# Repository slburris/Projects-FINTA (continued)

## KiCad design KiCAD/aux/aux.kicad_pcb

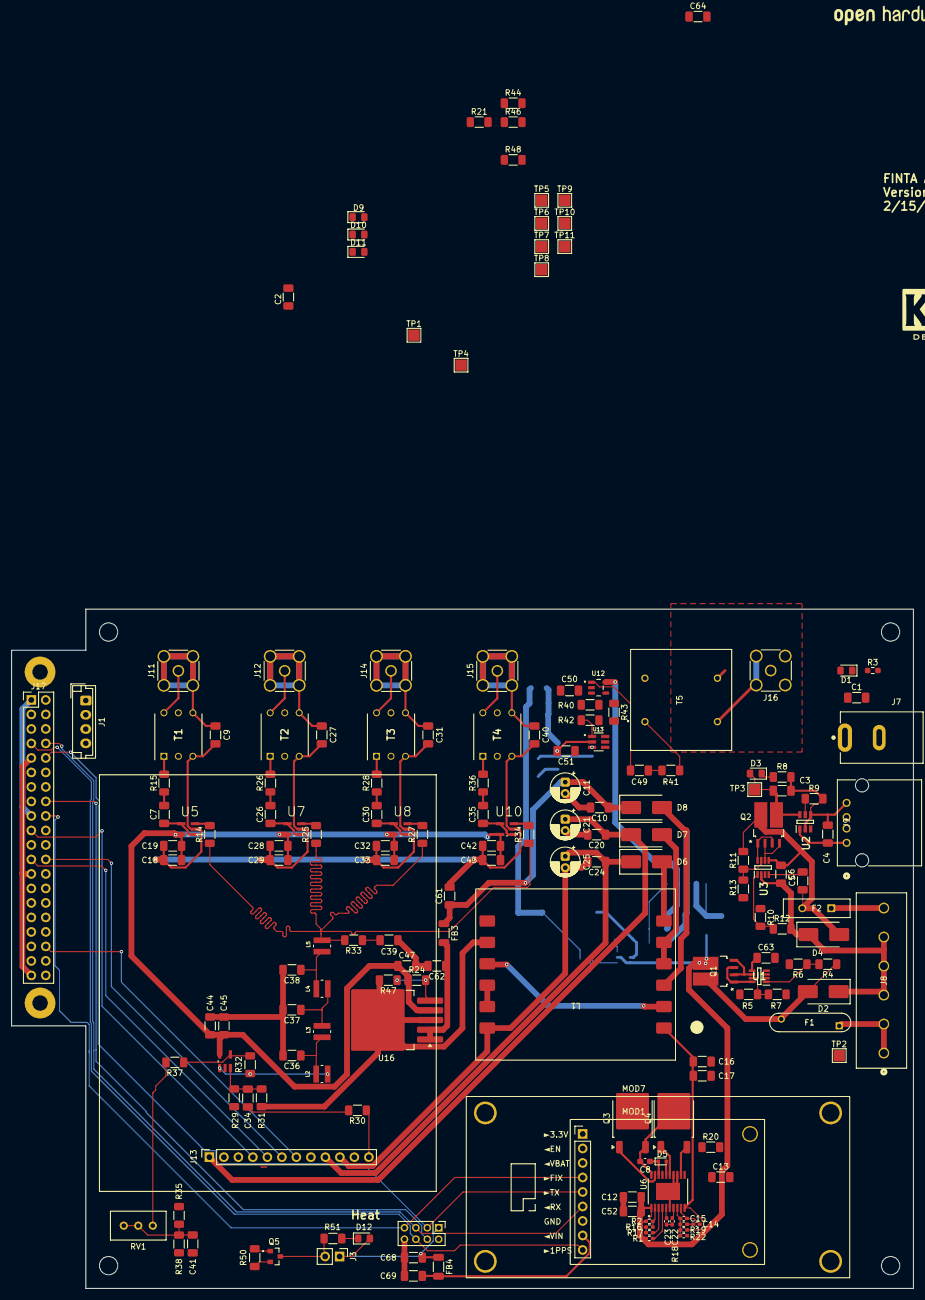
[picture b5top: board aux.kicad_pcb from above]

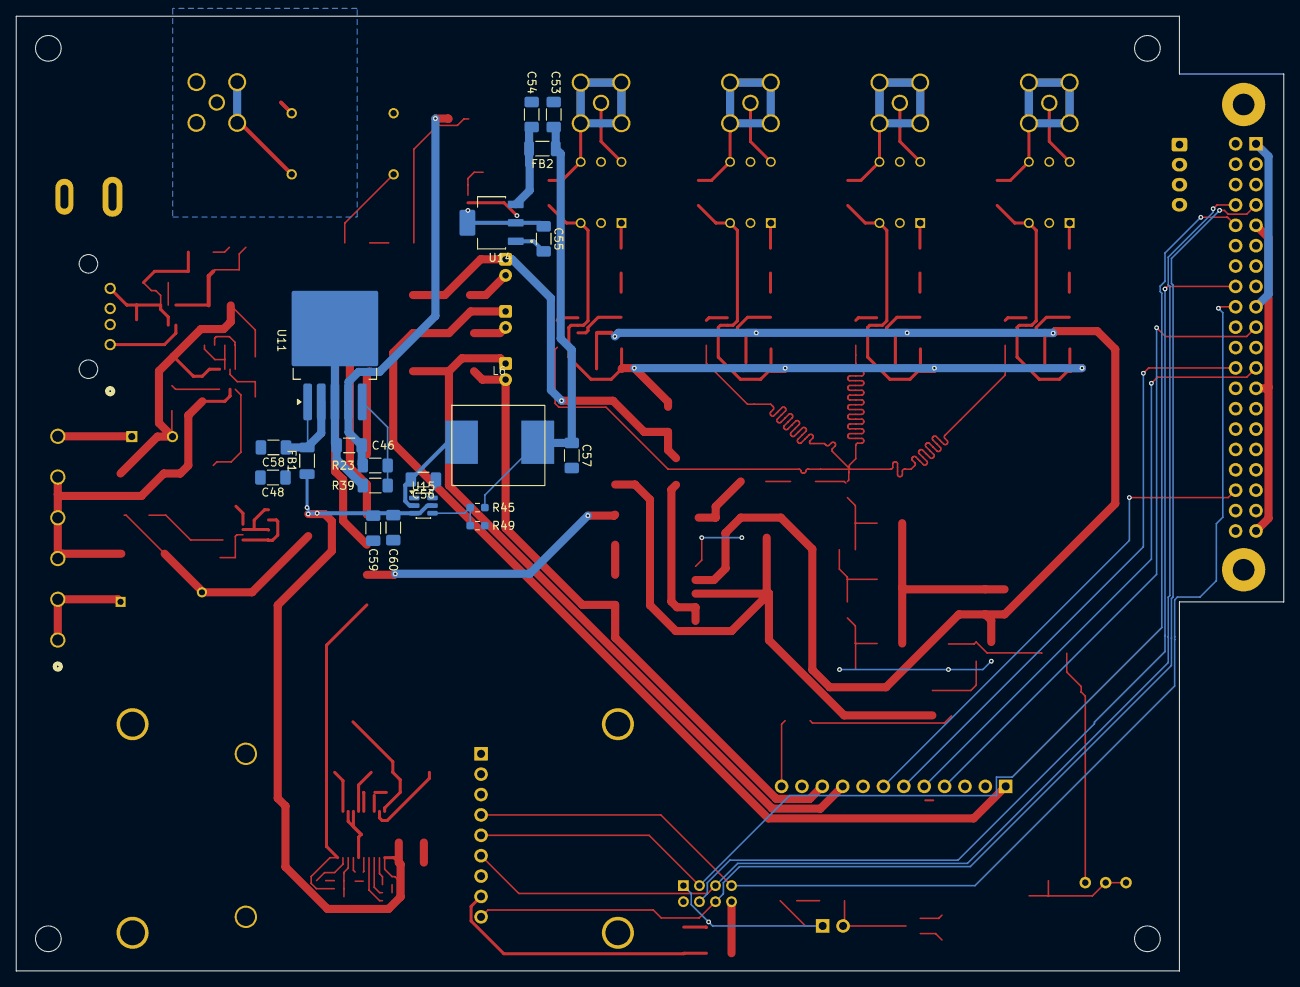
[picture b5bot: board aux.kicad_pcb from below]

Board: 2 copper layers, 158.0 x 119.0 mm, 200 parts (20 on the bottom side), 125 nets.

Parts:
C1, C3, C4, C10, C20, C24, C48, C49, C53, C54, C55, C58, C59, C61, C62, C68, C69: 10uf; C_1206_3216Metric_Pad1.33x1.80mm_HandSolder
C2, C5: 220nf; C_1206_3216Metric_Pad1.33x1.80mm_HandSolder
C6, C7, C18, C26, C28, C30, C32, C35, C39, C41, C42, C44, C51, C56, C60, C63, C64: 0.1uf; C_1206_3216Metric_Pad1.33x1.80mm_HandSolder
C8: 100nf; C_0603_1608Metric_Pad1.08x0.95mm_HandSolder
C9, C27, C31, C40: 0.01uf; C_1206_3216Metric_Pad1.33x1.80mm_HandSolder
C11, C21, C25: 100uf polymer; CP_Radial_D5.0mm_P2.00mm
C12, C46, C47, C52, C57: 22uf; C_1206_3216Metric_Pad1.33x1.80mm_HandSolder
C13: 1uf; C_1206_3216Metric_Pad1.33x1.80mm_HandSolder
C14: 82pf; C_0402_1005Metric_Pad0.74x0.62mm_HandSolder
C15: 5.1pf; C_0402_1005Metric_Pad0.74x0.62mm_HandSolder
C16, C17: 39uf; C_1206_3216Metric_Pad1.33x1.80mm_HandSolder
C19, C29, C33, C43, C45: 0.001uf; C_1206_3216Metric_Pad1.33x1.80mm_HandSolder
C22: 33nf; C_0402_1005Metric_Pad0.74x0.62mm_HandSolder
C23: 150pf; C_0402_1005Metric_Pad0.74x0.62mm_HandSolder
C34: 0.001uf C0G; C_1206_3216Metric_Pad1.33x1.80mm_HandSolder
C36, C38: 390; C_1206_3216Metric_Pad1.33x1.80mm_HandSolder
C37: 820; C_1206_3216Metric_Pad1.33x1.80mm_HandSolder
C50: 0.01uf C0G; C_1206_3216Metric_Pad1.33x1.80mm_HandSolder
D1, D3, D9, D10, D11, D12: LED; LED_0805_2012Metric_Pad1.15x1.40mm_HandSolder
D2, D4: SMBJ18CA; D_SMB_Handsoldering
D5: BAS516,115; D_SOD-523
D6, D7, D8: D_Schottky; D_SMB_Handsoldering
F1: RUEF500; FUSE_RUEF500_LTF
F2: RUEF250; FUS_RUEF250_TYCO_TYC
FB1, FB2, FB3, FB4: BLM31PG601; L_1206_3216Metric_Pad1.22x1.90mm_HandSolder
H1, H2, H3, H4, H5, H6: MountingHole; MountingHole_3.2mm_M3
H7, H8: MountingHole_Pad; MountingHole_2.7mm_M2.5_Pad
J1: Conn_01x04_Socket; JST_EH_B4B-EH-A_1x04_P2.50mm_Vertical
J3: Conn_01x02_Pin; PinHeader_1x02_P2.54mm_Vertical
J7: PJ-037A; CUI_PJ-037A
J8: 1758050; CONN_1758050
J9: CU01SAH0S00; CONN_CU01SAH0S00_CVI
J11, J12, J14, J15, J16: Conn_Coaxial_Small; SMA_Amphenol_132291-12_Vertical
J13: Conn_01x12_Socket; PinSocket_1x12_P2.54mm_Vertical
J17: Conn_02x20_Odd_Even; PinHeader_2x20_P2.54mm_Vertical
L1: HP6-0090L
L2, L3, L4, L5: VLS3015CX-1R0M-1; IND_VLS3015CX-1R0M-1
L6: 3.3uh; BCIHP10SC
MOD1: Adafruit Ultimate GPS Breakout v3
MOD7: Conn_02x04_Odd_Even; RCB-F9T-0
Q1, Q2: SQJ746ELP-T1_GE3; PowerPAK_SO-8L-2_DUAL_VIS
Q3, Q4: GSFD0650; TO-252-2
Q5: IRLML6344TRPBF; TRANS_IRLML6344TRPBF
R1: 1M; R_0402_1005Metric_Pad0.72x0.64mm_HandSolder
R2: 15.4K; R_0402_1005Metric_Pad0.72x0.64mm_HandSolder
R3: 2K; R_0603_1608Metric_Pad0.98x0.95mm_HandSolder
R4: 75K; R_1206_3216Metric_Pad1.30x1.75mm_HandSolder
R5: 107K; R_1206_3216Metric_Pad1.30x1.75mm_HandSolder
R6, R7, R12, R13, R21, R39, R47: 10K; R_1206_3216Metric_Pad1.30x1.75mm_HandSolder
R8, R35, R38, R44, R51: 560; R_1206_3216Metric_Pad1.30x1.75mm_HandSolder
R9: 3.3K; R_1206_3216Metric_Pad1.30x1.75mm_HandSolder
R10: 24.3K; R_1206_3216Metric_Pad1.30x1.75mm_HandSolder
R11: 36.5K; R_1206_3216Metric_Pad1.30x1.75mm_HandSolder
R14, R15, R25, R26, R27, R28, R33, R34, R36: 49.9; R_1206_3216Metric_Pad1.30x1.75mm_HandSolder
R16: 2.26K; R_0402_1005Metric_Pad0.72x0.64mm_HandSolder
R17: 25K; R_0402_1005Metric_Pad0.72x0.64mm_HandSolder
R18: 210K; R_0402_1005Metric_Pad0.72x0.64mm_HandSolder
R19: 50K; R_0402_1005Metric_Pad0.72x0.64mm_HandSolder
R20: 10mohm; R_1206_3216Metric_Pad1.30x1.75mm_HandSolder
R22: 11.5K; R_0402_1005Metric_Pad0.72x0.64mm_HandSolder
R23, R24: 78.7K; R_1206_3216Metric_Pad1.30x1.75mm_HandSolder
R29, R31: 47K; R_1206_3216Metric_Pad1.30x1.75mm_HandSolder
R30, R42, R43: 1K; R_1206_3216Metric_Pad1.30x1.75mm_HandSolder
R32: 2.7K; R_1206_3216Metric_Pad1.30x1.75mm_HandSolder
R37: 220; R_1206_3216Metric_Pad1.30x1.75mm_HandSolder
R40: 1.4K; R_1206_3216Metric_Pad1.30x1.75mm_HandSolder
R41: 600; R_1206_3216Metric_Pad1.30x1.75mm_HandSolder
R45: 68.4K; R_0603_1608Metric_Pad0.98x0.95mm_HandSolder
R46, R48: 1.8K; R_1206_3216Metric_Pad1.30x1.75mm_HandSolder
R49: 10K; R_0603_1608Metric_Pad0.98x0.95mm_HandSolder
R50: 100K; R_1206_3216Metric_Pad1.30x1.75mm_HandSolder
RV1: 2.5K; Potentiometer_Bourns_3296W_Vertical
T1, T2, T3, T4: WB1-1L; DIP762W64P254L826H572Q6N
T5: LM-NP-1001-B1L; LMNP1001B1L
TP1, TP2, TP3, TP4, TP5, TP6, TP7, TP8, TP9, TP10, TP11: TestPoint_Probe; TestPoint_Pad_2.0x2.0mm
U1, U3: AP74502QTA8-7; SOT65P280X110-8N
U2: AP22654WU-7; SOT95P280X82-6N
U5, U7, U8, U9, U10: AD8055ARTZ-R2; SOT95P290X145-5N
U6: LM25116MHX_NOPB; SOP65P640X110-21N
U11, U16: MIC29302WU; TO-263-5_TabPin3
U12: OPA171AIDBVR; SOT95P280X145-5NOPA171
U13: DAC121S101CIMKX_NOPB; SOT95P280X110-6N
U14: LDL1117S50R_; SOT230P700X180-4N
U15: TPS563201; SOT-23-6

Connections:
+12V: C1.1, C12.1, C48.1, C52.1, C59.1, C60.1, D1.2 (A), FB1.1, J7.1, Q1.6, R1.2, R2.2, TP1.1, U6.1 (VIN), U15.3 (VIN), U15.5 (EN)
/Distribution/10Mhz: J13.12, R30.1
/Distribution/Analog GND: C9.1, C10.2, C11.2, C18.2, C19.2, C27.1, C28.2, C29.2, C31.1, C32.2, C33.2, C36.2, C37.2, C38.2, C39.2, C40.1, C41.2, C42.2, C43.2, C44.2, C45.2, C47.2, C61.2, C62.2, L1.11, R31.1, R38.1, R47.2, R48.2, T1.3, T2.3, T3.3, T4.3, TP11.1, U5.2 (V-), U7.2 (V-), U8.2 (V-), U9.2 (V-), U10.2 (V-), U16.3 (GND)
/Distribution/Analog PWR: C18.1, C19.1, C28.1, C29.1, C32.1, C33.1, C42.1, C43.1, C44.1, C45.1, C47.1, D11.2 (A), R24.1, R29.2, R35.2, TP10.1, U5.5 (V+), U7.5 (V+), U8.5 (V+), U9.5 (V+), U10.5 (V+), U16.4 (VOUT)
/Distribution/Buffer1/SINEIN: L5.2, R14.1, R25.1, R27.1, R33.2, R34.1
/Distribution/Buffer1/XFMRGND: C9.2, J11.2 (Ext), T1.4
/Distribution/Buffer2/XFMRGND: C27.2, J12.2 (Ext), T2.4
/Distribution/Buffer3/XFMRGND: C31.2, J14.2 (Ext), T3.4
/Distribution/Buffer4/XFMRGND: C40.2, J15.2 (Ext), T4.4
/IRIG/+5V IN: C51.1, C55.1, D10.2 (A), TP6.1, U13.3 (VA), U14.2 (VOUT), U14.4 (VOUT__1)
/IRIG/+11V IN: C46.1, C64.1, D9.2 (A), R23.1, TP9.1, U11.4 (VOUT), U12.5
/IRIG/IRIGGND: J16.2 (Ext), T5.8
/IRIG/SPI_IRIG_SCLK: J17.40, U13.5 (SCLK)
/IRIG/~SPI_IRIG_CS: J17.12, U13.6 (~SYNC)
/connectors/1PPS_FROM_GPS: J17.7, MOD1.9 (◄1PPS), MOD7.6 (TP1)
/connectors/10Mhz Disciplined: J13.7, J17.36
/connectors/Kria 3.3V: J13.3, J17.1, J17.17, MOD7.2 (VCC)
/connectors/Kria 5V: C68.1, D12.2 (A), FB4.1, J3.1, J17.2, J17.4, MOD7.1 (VCC_ANT)
/connectors/RX_TO_GPS: J17.10, MOD1.5 (◄TX), MOD7.3 (TXD)
/connectors/SCL: J1.4, J17.13
/connectors/SDA: J1.3, J17.11
/connectors/SPI_MOSI: J13.4, J17.19
/connectors/SPI_SCLK: J13.5, J17.23
/connectors/TX_FROM_GPS: J17.8, MOD1.6 (►RX), MOD7.5 (RXD)
/connectors/~SPI_OCXO_CS: J13.6, J17.24
/ocxo/+6V Analog: C24.1, C25.1, D6.1 (K), J13.9
/ocxo/+6V Oven: C20.1, C21.1, D7.1 (K), J13.1
/ocxo/GND Analog: C24.2, C25.2, J13.10, L1.7, TP8.1
/ocxo/GND Oven: C20.2, C21.2, J13.2, L1.8, L1.9, TP5.1
/power_connectors/+5Vin: F2.1, J8.6, TP4.1
/power_connectors/+12Vin: F1.1, J8.1, J8.2, TP2.1
GND: C1.2, C3.2, C4.2, C6.2, C12.2, C13.2, C16.2, C17.2, C22.2, C23.2, C46.2, C48.2, C50.2, C51.2, C52.2, C53.2, C54.2, C55.2, C57.2, C58.2, C59.2, C60.2, C63.2, C64.2, C68.2, C69.2, D2.1 (A1), D4.1 (A1), J1.1, J7.2, J8.3, J8.4, J8.5, J9.4, J13.8, J17.6, J17.9, J17.14, J17.20, J17.25, J17.30, J17.34, J17.39, MOD1.7 (GND), MOD7.8 (GND), Q5.2, R3.2, R6.2, R7.2, R8.2, R9.2, R12.2, R13.2, R16.1, R17.1, R20.2, R21.2, R22.1, R39.2, R43.2, R44.2, R46.2, R49.2, R50.2, T5.4, U1.2 (GND), U2.2 (GND), U2.4 (EN/~EN), U3.2 (GND), U6.6 (AGND), U6.13 (CSG), U6.14 (PGND), U6.21 (EP), U11.3 (GND), U12.2, U13.2 (GND), U14.1 (GND), U15.1 (GND)
unnamed: C7.2, R15.1
unnamed: C14.2, R18.2
unnamed: C26.2, R26.1
unnamed: C30.2, R28.1
unnamed: C34.1, R30.2
unnamed: C35.2, R36.1
unnamed: C36.1, L2.2, L3.1
unnamed: C37.1, L3.2, L4.1
unnamed: C38.1, L4.2, L5.1
unnamed: C39.1, R33.1
unnamed: C41.1, R35.1, R38.2, RV1.1, RV1.2
unnamed: C49.1, R40.2, U12.1
unnamed: C49.2, R41.1
unnamed: C50.1, R42.2, U12.3
unnamed: C53.1, C57.1, FB2.1, L6.2, R45.1, TP7.1
unnamed: D1.1 (K), R3.1
unnamed: C2.1, C63.1, D2.2 (A2), F1.2, Q1.5, R4.1, R5.1, U1.5 (VIN)
unnamed: C3.1, D3.2 (A), Q2.6, TP3.1, U2.6 (IN)
unnamed: D3.1 (K), R8.1
unnamed: C5.1, C6.1, D4.2 (A2), F2.2, Q2.5, R10.1, R11.1, U3.5 (VIN)
unnamed: C13.1, D5.2 (A), Q3.2 (D), U6.16 (VCC)
unnamed: C8.1, D5.1 (K), U6.18 (HB)
unnamed: D6.2 (A), L1.6
unnamed: D7.2 (A), L1.4, L1.5
unnamed: D8.2 (A), L1.3
unnamed: C10.1, C11.1, C61.1, D8.1 (K), FB3.1
unnamed: D9.1 (K), R46.1
unnamed: D10.1 (K), R44.1
unnamed: D11.1 (K), R48.1
unnamed: D12.1 (K), R51.1
unnamed: J3.2, Q5.3, R51.2
unnamed: J11.1 (In), T1.6
unnamed: J12.1 (In), T2.6
unnamed: J14.1 (In), T3.6
unnamed: J15.1 (In), T4.6
unnamed: J16.1 (In), T5.5
unnamed: J17.16, MOD1.2 (►EN), MOD7.4 (RST)
unnamed: J17.18, MOD1.4 (◄FIX), MOD7.7 (TP2)
unnamed: J17.32, Q5.1, R50.1
unnamed: L1.2, L1.10
unnamed: L2.1, R32.2, U9.1
unnamed: C69.1, FB4.2, MOD1.8 (►VIN)
unnamed: Q3.1 (G), U6.19 (HO)
unnamed: C8.2, L1.12, Q3.3 (S), Q4.2 (D), U6.20 (SW)
unnamed: Q4.1 (G), U6.15 (LO)
unnamed: Q4.3 (S), R20.1, U6.12 (CS)
unnamed: R15.2, T1.1
unnamed: R26.2, T2.1
unnamed: R28.2, T3.1
unnamed: R36.2, T4.1
unnamed: R37.2, RV1.3
unnamed: R40.1, R43.1, U12.4
unnamed: R41.2, T5.1
unnamed: R4.2, R6.1, U1.1 (EN/UVLO)
unnamed: Q1.2, Q1.4, U1.6 (GATE)
unnamed: R5.2, R7.1, U1.7 (OVLO)
unnamed: Q1.1, Q1.3, U1.8 (SRC)
unnamed: C2.2, U1.4 (VCP)
unnamed: R9.1, U2.5 (ILIM)
unnamed: C4.1, J9.1, U2.1 (OUT)
unnamed: R10.2, R12.1, U3.1 (EN/UVLO)
unnamed: Q2.2, Q2.4, U3.6 (GATE)
unnamed: R11.2, R13.1, U3.7 (OVLO)
unnamed: Q2.1, Q2.3, U3.8 (SRC)
unnamed: C5.2, U3.4 (VCP)
unnamed: R14.2, U5.3 (+)
unnamed: C7.1, U5.1, U5.4 (-)
unnamed: C14.1, C15.1, U6.9 (COMP)
unnamed: R21.1, U6.11 (DEMB)
unnamed: R1.1, U6.4 (EN)
unnamed: C15.2, R18.1, R19.1, R22.2, U6.8 (FB)
unnamed: C23.1, U6.5 (RAMP)
unnamed: R17.2, U6.3 (RT/SYNC)
unnamed: C22.1, U6.7 (SS)
unnamed: R2.1, R16.2, U6.2 (UVLO)
unnamed: C16.1, C17.1, L1.1, R19.2, U6.10 (VOUT), U6.17 (VCCX)
unnamed: R25.2, U7.3 (+)
unnamed: C26.1, U7.1, U7.4 (-)
unnamed: R27.2, U8.3 (+)
unnamed: C30.1, U8.1, U8.4 (-)
unnamed: C34.2, R29.1, R31.2, U9.3 (+)
unnamed: R32.1, R37.1, U9.4 (-)
unnamed: R34.2, U10.3 (+)
unnamed: C35.1, U10.1, U10.4 (-)
unnamed: R23.2, R39.1, U11.5 (ADJ)
unnamed: C58.1, FB1.2, U11.1 (EN), U11.2 (VIN)
unnamed: R42.1, U13.1 (VOUT)
unnamed: C54.1, FB2.2, U14.3 (VIN)
unnamed: C56.2, L6.1, U15.2 (SW)
unnamed: C56.1, U15.6 (VBST)
unnamed: R45.2, R49.1, U15.4 (VFB)
unnamed: R24.2, R47.1, U16.5 (ADJ)
unnamed: C62.1, FB3.2, U16.1 (EN), U16.2 (VIN)

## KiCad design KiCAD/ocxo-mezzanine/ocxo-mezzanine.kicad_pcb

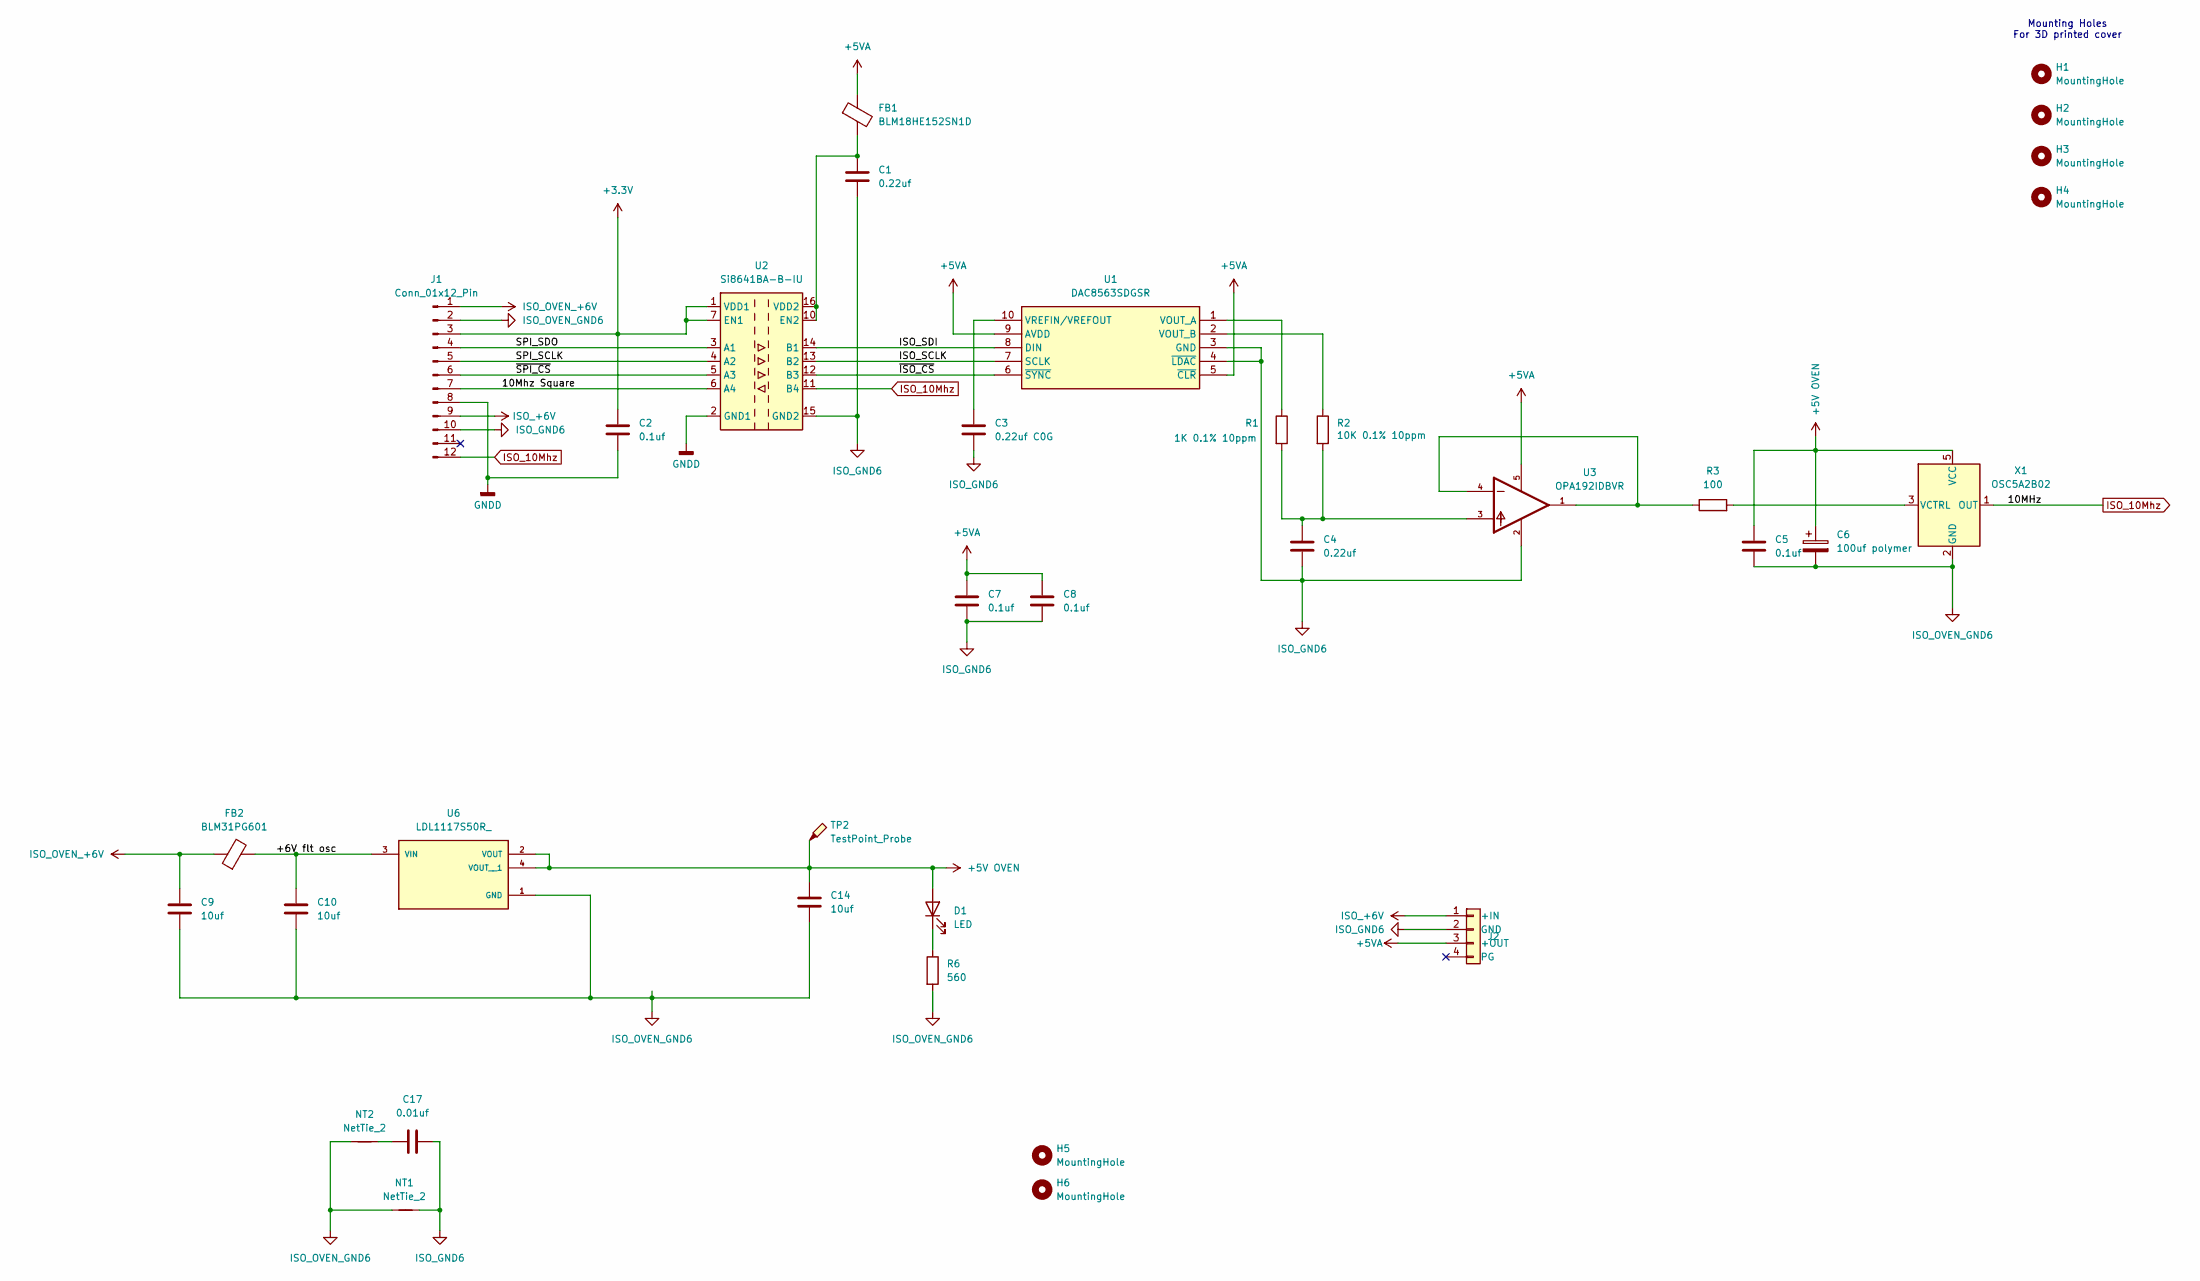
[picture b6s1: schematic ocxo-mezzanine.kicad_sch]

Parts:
C1, C4: 0.22uf; C_1206_3216Metric_Pad1.33x1.80mm_HandSolder
C2, C5, C7, C8: 0.1uf; C_1206_3216Metric_Pad1.33x1.80mm_HandSolder
C3: 0.22uf C0G; C_0603_1608Metric_Pad1.08x0.95mm_HandSolder
C6: 100uf polymer; CP_Radial_D5.0mm_P2.00mm
C9, C10, C14: 10uf; C_1206_3216Metric_Pad1.33x1.80mm_HandSolder
C17: 0.01uf; C_0603_1608Metric_Pad1.08x0.95mm_HandSolder
D1: LED; LED_0805_2012Metric_Pad1.15x1.40mm_HandSolder
FB1: BLM18HE152SN1D; L_0603_1608Metric_Pad1.05x0.95mm_HandSolder
FB2: BLM31PG601; L_1206_3216Metric_Pad1.22x1.90mm_HandSolder
H1, H2, H3, H4, H5, H6: MountingHole; MountingHole_3.2mm_M3
J1: Conn_01x12_Pin; PinHeader_1x12_P2.54mm_Vertical
J2: lownoise-LDO
NT1, NT2: NetTie_2; NetTie-2_SMD_Pad0.5mm
R1: 1K 0.1% 10ppm; R_0603_1608Metric_Pad0.98x0.95mm_HandSolder
R2: 10K 0.1% 10ppm; R_0603_1608Metric_Pad0.98x0.95mm_HandSolder
R3: 100; R_1206_3216Metric_Pad1.30x1.75mm_HandSolder
R6: 560; R_1206_3216Metric_Pad1.30x1.75mm_HandSolder
TP2: TestPoint_Probe; TestPoint_Pad_2.0x2.0mm
U1: DAC8563SDGSR; SOP50P490X110-10N; Manufacturer_Part_Number DAC8563SDGSR; Mouser Part Number 595-DAC8563SDGSR
U2: Si8641BA-B-IU; QSOP-16_3.9x4.9mm_P0.635mm
U3: OPA192IDBVR; SOT95P280X145-5N; PARTREV F
U6: LDL1117S50R_; SOT230P700X180-4N; PARTREV 7
X1: OSC5A2B02; CTI-OSC-25x25

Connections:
+3.3V: C2.2, J1.3, U2.1 (VDD1), U2.7 (EN1)
+5V OVEN: C5.1, C6.1, C14.1, D1.2 (A), TP2.1, U6.2 (VOUT), U6.4 (VOUT__1), X1.5 (VCC)
+5VA: C7.1, C8.1, FB1.1, J2.3 (+OUT), U1.5 (~CLR), U1.9 (AVDD), U3.5
/10Mhz Square: J1.7, U2.6 (A4)
/+6V flt osc: C10.1, FB2.2, U6.3 (VIN)
/ISO_SCLK: U1.7 (SCLK), U2.13 (B2)
/ISO_SDI: U1.8 (DIN), U2.14 (B1)
/SPI_SCLK: J1.5, U2.4 (A2)
/SPI_SDO: J1.4, U2.3 (A1)
/~ISO_CS: U1.6 (~SYNC), U2.12 (B3)
/~SPI_CS: J1.6, U2.5 (A3)
GNDD: C2.1, J1.8, U2.2 (GND1), U2.8 (GND1)
ISO_10Mhz: J1.12, U2.11 (B4), X1.1 (OUT)
ISO_+6V: J1.9, J2.1 (+IN)
ISO_GND6: C1.2, C3.2, C4.2, C7.2, C8.2, C17.2, J1.10, J2.2 (GND), NT1.2, U1.3 (GND), U1.4 (~LDAC), U2.9 (GND2), U2.15 (GND2), U3.2
ISO_OVEN_+6V: C9.1, FB2.1, J1.1
ISO_OVEN_GND6: C5.2, C6.2, C9.2, C10.2, C14.2, J1.2, NT1.1, NT2.1, R6.2, U6.1 (GND), X1.2 (GND)
unnamed: C4.1, R1.2, R2.2, U3.3
unnamed: C17.1, NT2.2
unnamed: D1.1 (K), R6.1
unnamed: R3.1, U3.1, U3.4
unnamed: R1.1, U1.1 (VOUT_A)
unnamed: R2.1, U1.2 (VOUT_B)
unnamed: C3.1, U1.10 (VREFIN/VREFOUT)
unnamed: C1.1, FB1.2, U2.10 (EN2), U2.16 (VDD2)
unnamed: R3.2, X1.3 (VCTRL)

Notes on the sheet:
Mounting Holes For 3D printed cover

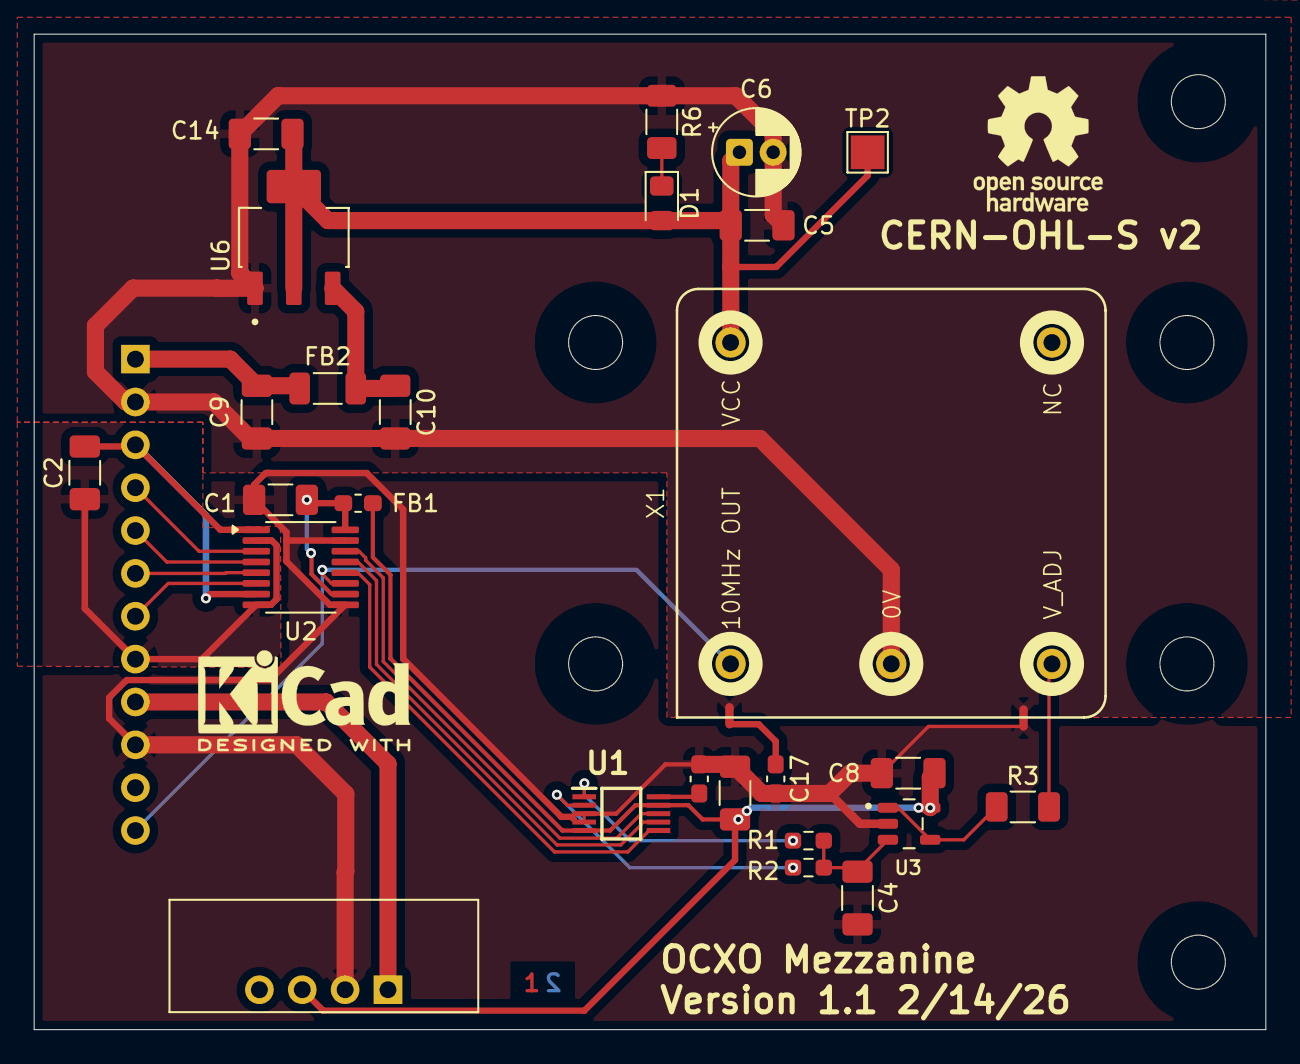
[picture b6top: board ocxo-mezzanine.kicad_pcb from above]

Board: 2 copper layers, 73.0 x 59.0 mm, 35 parts (1 on the bottom side), 26 nets.

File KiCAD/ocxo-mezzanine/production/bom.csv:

Designator,Footprint,Quantity,Value,LCSC Part #
"C1, C4",1206,2,0.22uf,
"C10, C14, C9",1206,3,10uf,
C17,0603,1,0.01uf,
"C2, C5, C7, C8",1206,4,0.1uf,
C3,0603,1,0.22uf C0G,
C6,CP_Radial_D5.0mm_P2.00mm,1,100uf polymer,
D1,0805,1,LED,
FB1,0603,1,BLM18HE152SN1D,
FB2,1206,1,BLM31PG601,
J1,PinHeader_1x12_P2.54mm_Vertical,1,Conn_01x12_Pin,
J2,lownoise-LDO,1,lownoise-LDO,
R1,0603,1,1K 0.1% 10ppm,
R2,0603,1,10K 0.1% 10ppm,
R3,1206,1,100,
R6,1206,1,560,
TP2,TestPoint_Pad_2.0x2.0mm,1,TestPoint_Probe,
U1,SOP50P490X110-10N,1,DAC8563SDGSR,
U2,QSOP-16_3.9x4.9mm_P0.635mm,1,Si8641BA-B-IU,
U3,SOT95P280X145-5N,1,OPA192IDBVR,
U6,SOT230P700X180-4N,1,LDL1117S50R_,
X1,CTI-OSC-25x25,1,OSC5A2B02,

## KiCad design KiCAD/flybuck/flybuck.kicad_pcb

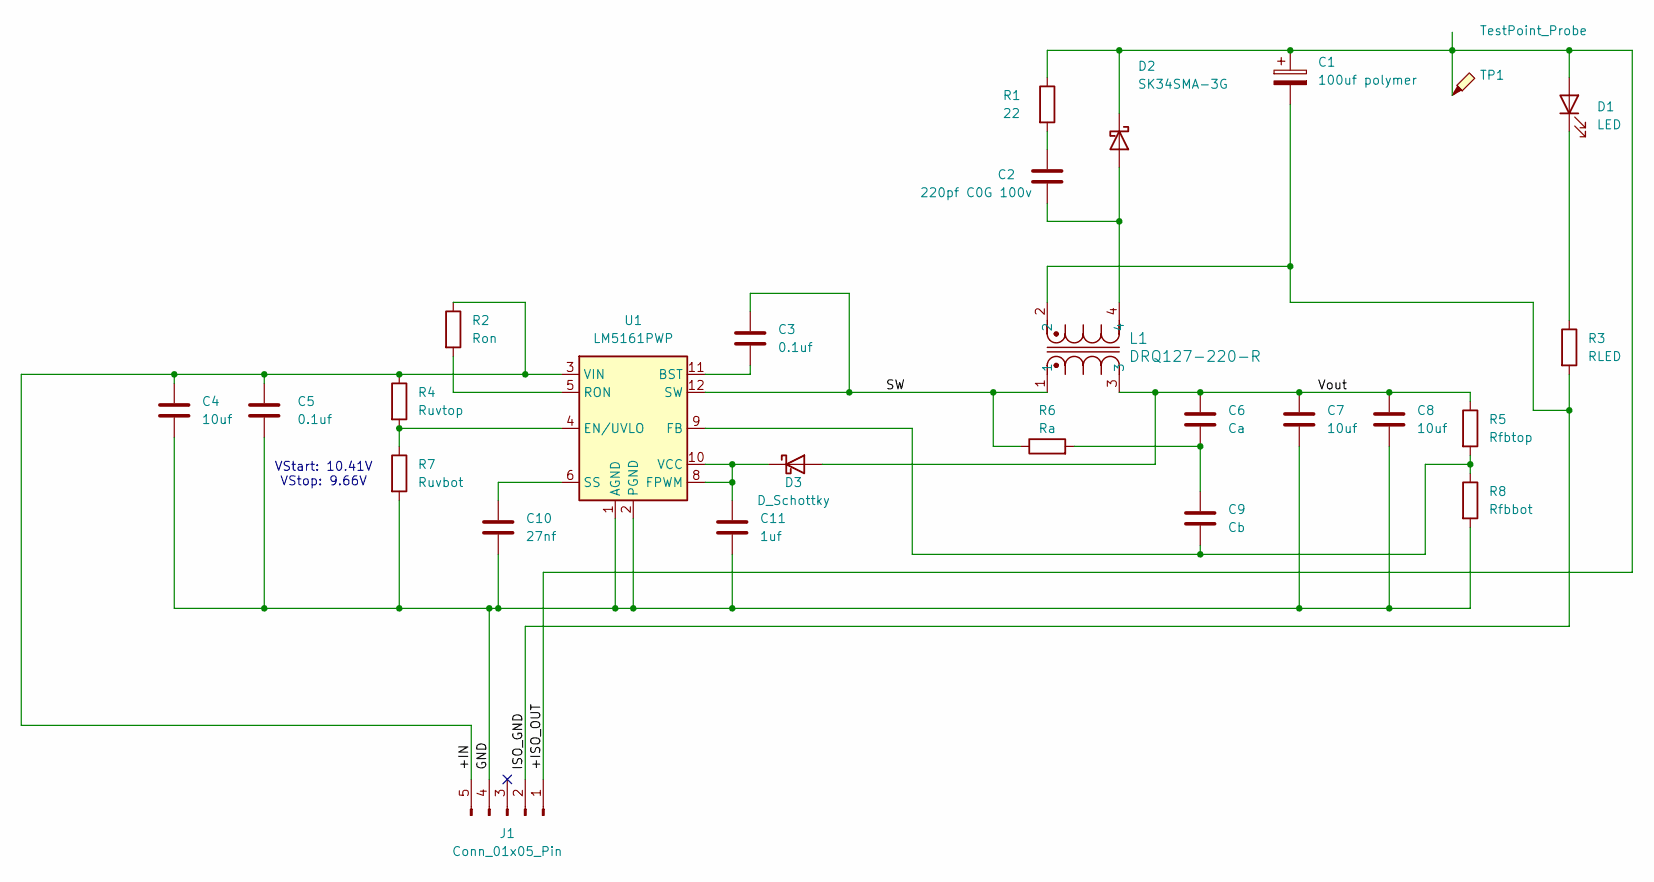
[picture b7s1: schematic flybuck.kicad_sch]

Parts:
C1: 100uf polymer; CP_Radial_D5.0mm_P2.00mm
C2: 220pf C0G 100v; C_1206_3216Metric_Pad1.33x1.80mm_HandSolder
C3, C5: 0.1uf; C_0603_1608Metric_Pad1.08x0.95mm_HandSolder
C4, C7, C8: 10uf; C_0603_1608Metric_Pad1.08x0.95mm_HandSolder
C6: Ca; C_0603_1608Metric_Pad1.08x0.95mm_HandSolder
C9: Cb; C_0603_1608Metric_Pad1.08x0.95mm_HandSolder
C10: 27nf; C_0603_1608Metric_Pad1.08x0.95mm_HandSolder
C11: 1uf; C_0603_1608Metric_Pad1.08x0.95mm_HandSolder
D1: LED; LED_D3.0mm_Horizontal_O1.27mm_Z2.0mm
D2: SK34SMA-3G; D_SMA_Handsoldering
D3: D_Schottky; D_SMA_Handsoldering
J1: Conn_01x05_Pin; PinHeader_1x05_P2.54mm_Horizontal
L1: DRQ127-220-R; DRQ127
R1: 22; R_1206_3216Metric_Pad1.30x1.75mm_HandSolder
R2: Ron; R_0603_1608Metric_Pad0.98x0.95mm_HandSolder
R3: RLED; R_1206_3216Metric_Pad1.30x1.75mm_HandSolder
R4: Ruvtop; R_0603_1608Metric_Pad0.98x0.95mm_HandSolder
R5: Rfbtop; R_0603_1608Metric_Pad0.98x0.95mm_HandSolder
R6: Ra; R_0603_1608Metric_Pad0.98x0.95mm_HandSolder
R7: Ruvbot; R_0603_1608Metric_Pad0.98x0.95mm_HandSolder
R8: Rfbbot; R_0603_1608Metric_Pad0.98x0.95mm_HandSolder
TP1: TestPoint_Probe; TestPoint_Pad_2.0x2.0mm
U1: LM5161PWP; Texas_HTSSOP-14-1EP_4.4x5mm_P0.65mm_EP3.4x5mm_Mask3.155x3.2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

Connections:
/+IN: C4.1, C5.1, J1.5, R2.1, R4.1, U1.3 (VIN)
/+ISO_OUT: C1.1, D1.2 (A), D2.1 (K), J1.1, R1.1, TP1.1
/GND: C4.2, C5.2, C7.2, C8.2, C10.2, C11.2, J1.4, R7.2, R8.2, U1.1 (AGND), U1.2 (PGND), U1.15 (AGND)
/ISO_GND: C1.2, J1.2, L1.2, R3.2
/SW: C3.1, L1.1, R6.1, U1.12 (SW), U1.13 (SW)
/Vout: C6.1, C7.1, C8.1, D3.2 (A), L1.3, R5.1
unnamed: C2.1, R1.2
unnamed: C6.2, C9.1, R6.2
unnamed: D1.1 (K), R3.1
unnamed: C2.2, D2.2 (A), L1.4
unnamed: C11.1, D3.1 (K), U1.8 (FPWM), U1.10 (VCC)
unnamed: C3.2, U1.11 (BST)
unnamed: R4.2, R7.1, U1.4 (EN/UVLO)
unnamed: C9.2, R5.2, R8.1, U1.9 (FB)
unnamed: R2.2, U1.5 (RON)
unnamed: C10.1, U1.6 (SS)

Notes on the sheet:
VStart: 10.41V VStop: 9.66V

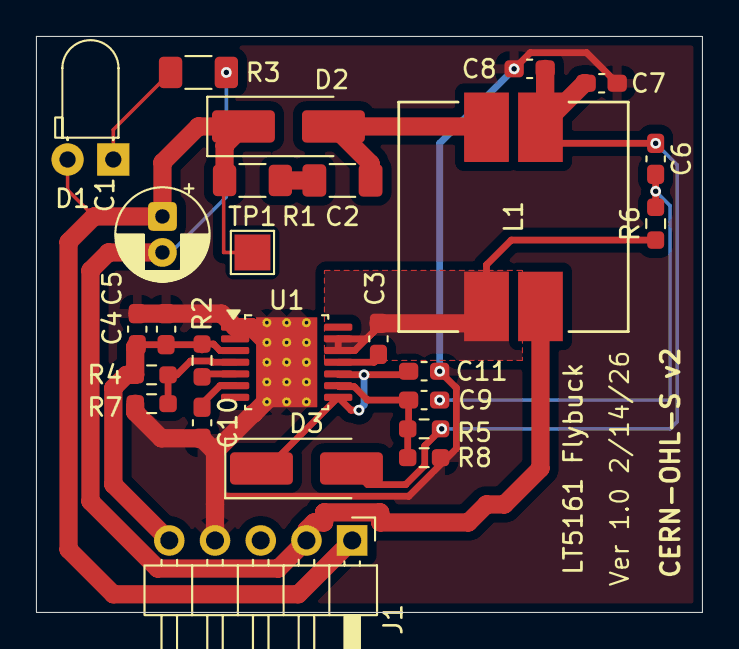
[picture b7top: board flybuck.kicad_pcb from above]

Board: 2 copper layers, 37.0 x 32.0 mm, 26 parts (0 on the bottom side), 16 nets.

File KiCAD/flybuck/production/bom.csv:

Designator,Footprint,Quantity,Value,LCSC Part #
C1,CP_Radial_D5.0mm_P2.00mm,1,100uf polymer,
C10,0603,1,27nf,
C11,0603,1,1uf,
C2,1206,1,220pf C0G 100v,
"C3, C5",0603,2,0.1uf,
"C4, C7, C8",0603,3,10uf,
C6,0603,1,Ca,
C9,0603,1,Cb,
D1,LED_D3.0mm_Horizontal_O1.27mm_Z2.0mm,1,LED,
D2,D_SMA_Handsoldering,1,SK34SMA-3G,
D3,D_SMA_Handsoldering,1,D_Schottky,
J1,PinHeader_1x05_P2.54mm_Horizontal,1,Conn_01x05_Pin,
L1,DRQ127,1,DRQ127-220-R,
R1,1206,1,22,
R2,0603,1,Ron,
R3,1206,1,RLED,
R4,0603,1,Ruvtop,
R5,0603,1,Rfbtop,
R6,0603,1,Ra,
R7,0603,1,Ruvbot,
R8,0603,1,Rfbbot,
TP1,TestPoint_Pad_2.0x2.0mm,1,TestPoint_Probe,
U1,Texas_HTSSOP-14-1EP_4.4x5mm_P0.65mm_EP3.4x5mm_Mask3.155x3.255mm_ThermalVias,1,LM5161PWP,
